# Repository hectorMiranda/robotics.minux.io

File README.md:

## Projects

### Marcebot

The Marcebot is a small, autonomous robot designed for navigation and object avoidance. It uses a differential drive system with two stepper motors and an ultrasonic sensor for obstacle detection. The robot's behavior is controlled by an Arduino Nano, which runs a program that implements three modes: collision avoidance, dead reckoning, and path planning.

- **Collision Avoidance Mode**: The robot moves forward and uses the ultrasonic sensor to detect obstacles. When an obstacle is detected, the robot stops, moves backward, and turns to avoid the obstacle.
- **Dead Reckoning Mode**: The robot follows a predefined path of forward movements and turns.
- **Path Planning Mode**: The robot navigates a path while avoiding obstacles.

The `arduino/marcebot` directory contains the Arduino code for the robot, including the main `.ino` file and the `Robot` class, which provides an API for controlling the robot's movements.

### Digital Clock

This project is a digital clock with an alarm function, built using an ATmega328P microcontroller and a 7-segment display. The clock displays the time in 12-hour format and includes a PM indicator. The user can set the time and alarm using pushbuttons. When the alarm is triggered, it plays a Pac-Man-themed melody.

The `arduino/clock` directory contains the Arduino code for the clock, including the main `.ino` file and the logic for the alarm and display.

### Baremetal Minux

This project is a lightweight, ncurses-based file explorer with multi-tab support and modern features, designed for minimal resource usage and maximum efficiency. It also includes a cryptocurrency wallet and camera functionality.

The `baremetal` directory contains the source code for the file explorer, including the main `minux.cpp` file, the `explorer.cpp` file, and the `error_console.cpp` file, which implements a DOOM-style error console.

### CUDA Status Checker

This project is a Python script that checks the status of the CUDA installation on a system. It verifies the NVIDIA driver, CUDA Toolkit, and CUDA runtime libraries, and it also checks for PyTorch and TensorFlow CUDA support.

The `cuda` directory contains the `cuda_status.py` script.

### ESP32-S3 Camera

This project is a simple web server that streams video from an ESP32-S3 camera module. The server provides a web page with an MJPEG stream from the camera.

The `esp32-s3-cam` directory contains the C++ code for the camera server.

### Galileo

This project contains a collection of Arduino and Python scripts for the Intel Galileo board. The Arduino scripts include examples for creating a web server, an interactive web server, and a Wi-Fi web server with Telnet. The Python scripts include examples for controlling motors and reading from sensors.

The `galileo` directory contains the Arduino and Python scripts.

### GoPiGo

This project is a Python library for controlling the GoPiGo robot. The library provides a simple API for controlling the robot's motors, reading from sensors, and controlling the LEDs.

The `raspberrypi/src` directory contains the `gopigo.py` library.

### SolidWorks

This project contains the SolidWorks assembly files for the MIT-101 project.

The `solidworks` directory contains the SolidWorks files.

## License

This project is licensed under the MIT License. See the `LICENSE` file for details.

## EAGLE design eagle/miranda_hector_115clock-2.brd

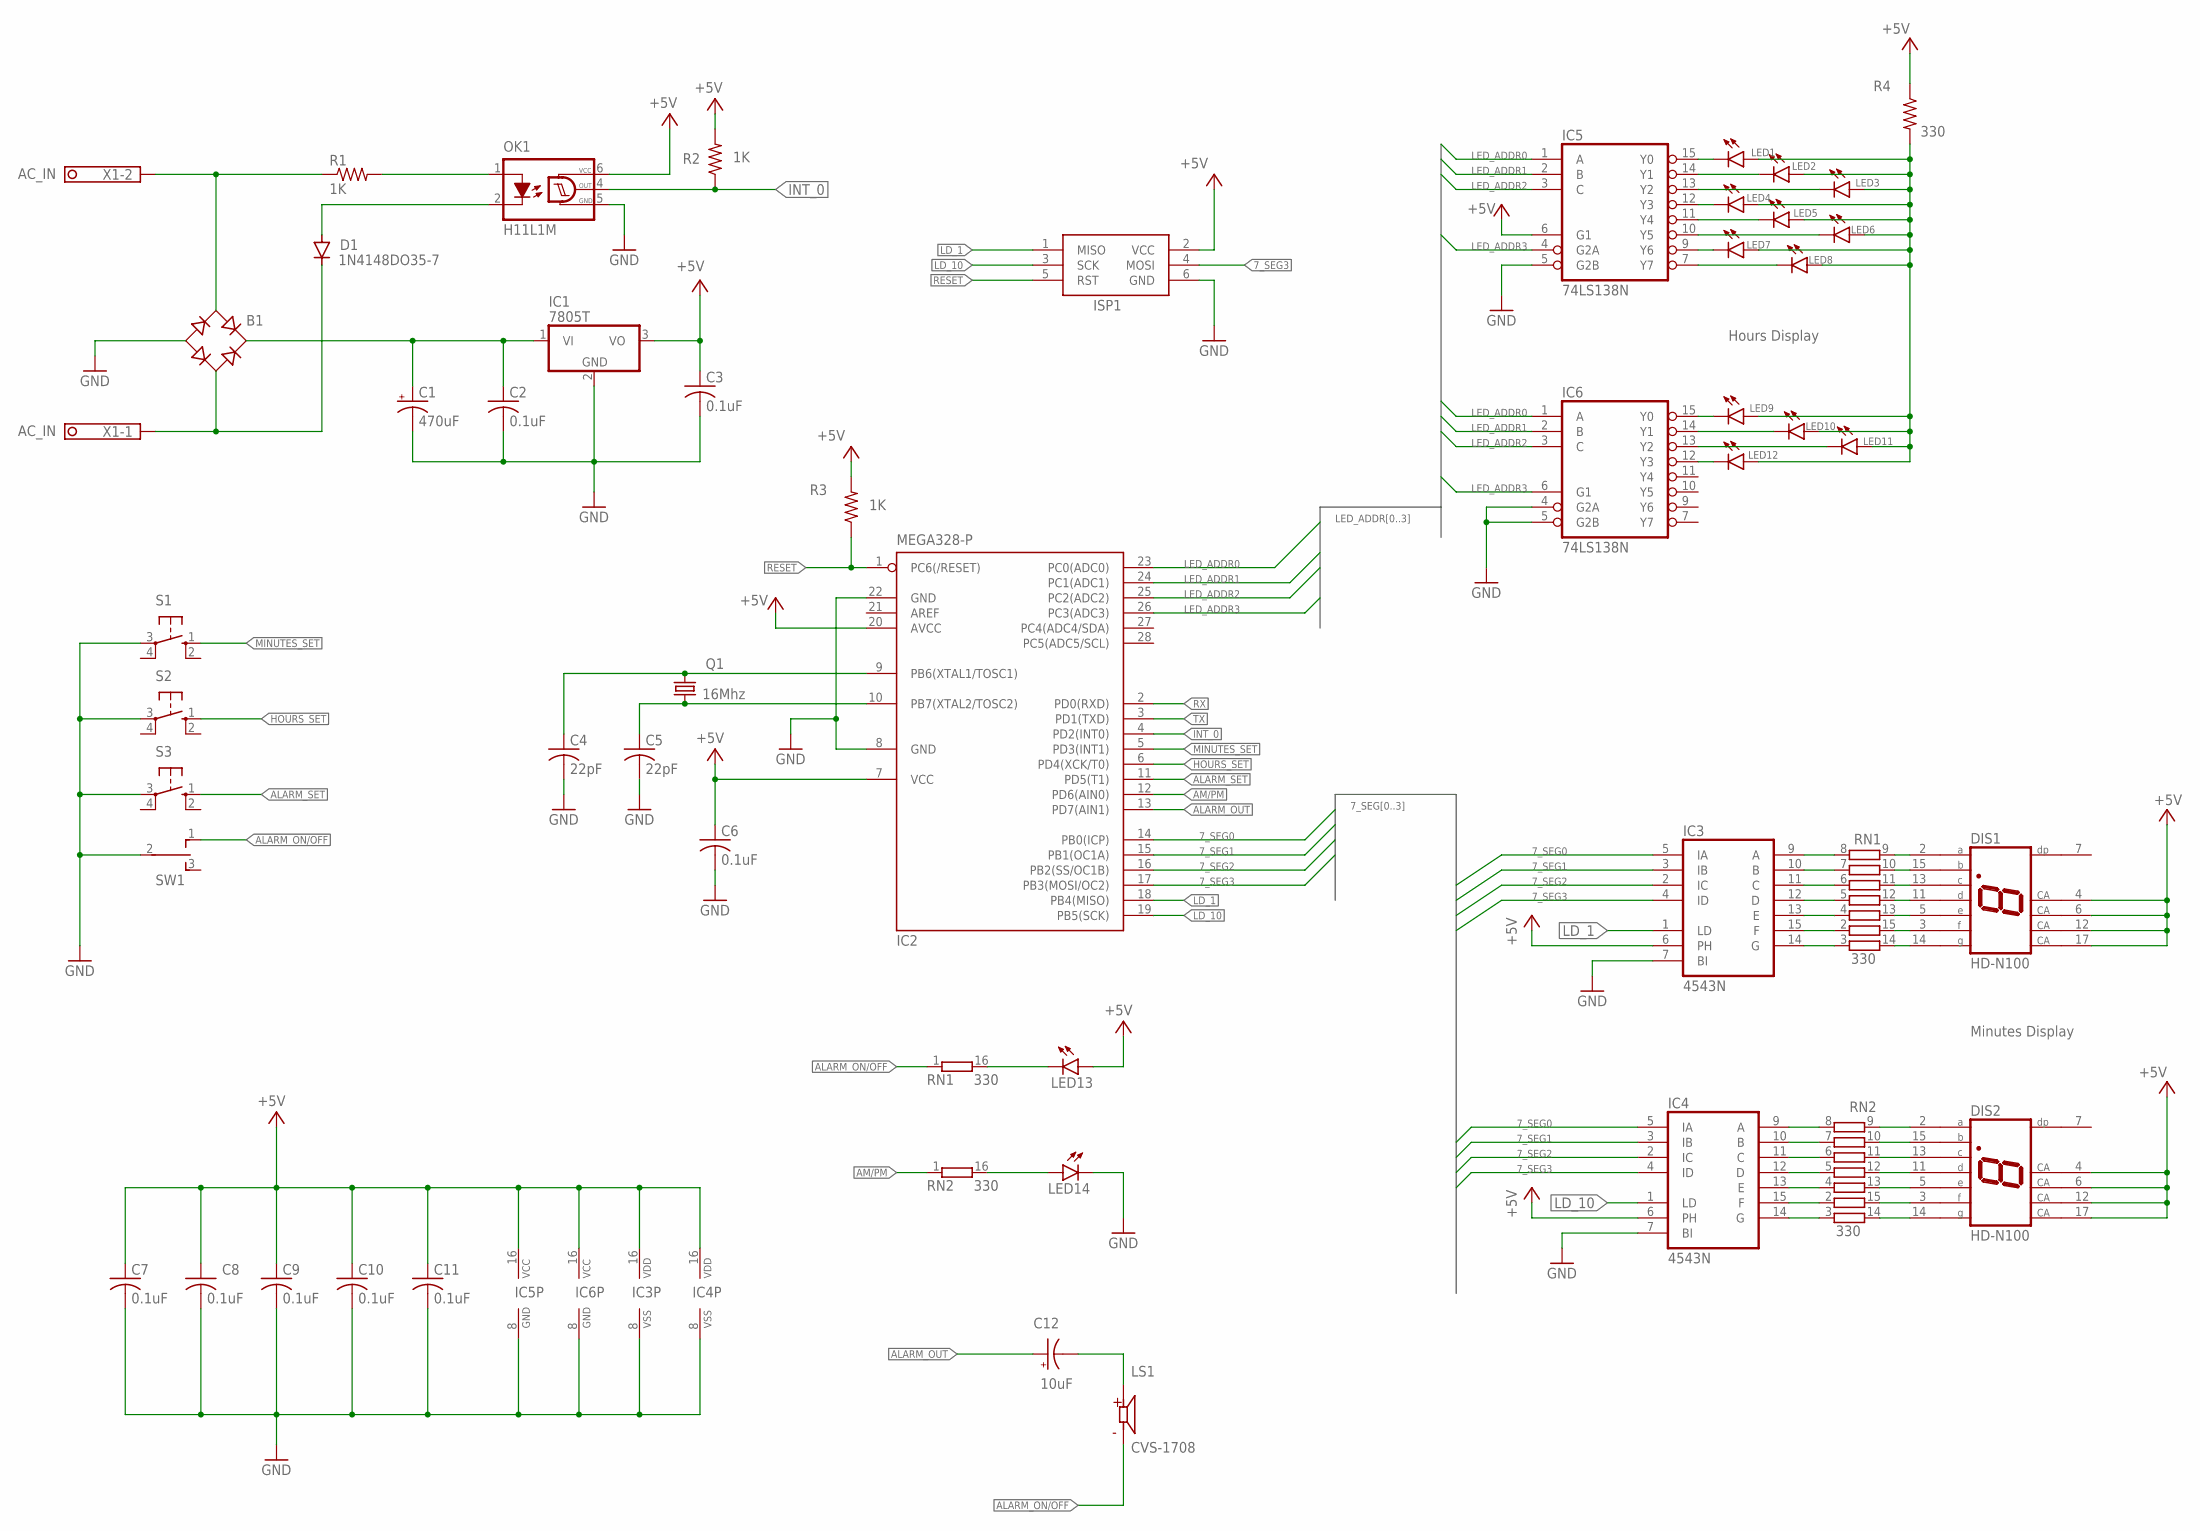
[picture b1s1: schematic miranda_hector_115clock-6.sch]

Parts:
B1: B-DIL
C1: 470uF; E3,5-8
C2, C3, C6, C7, C8, C9, C10, C11: 0.1uF; C025-025X050
C4, C5: 22pF; C025-025X050
C12: 10uF; E2,5-6E
D1: 1N4148DO35-7; DO35-7
DIS1, DIS2: HD-N100; HDSP-Q
IC1: 7805T; TO220H
IC2: MEGA328-P; DIL28-3
IC3, IC4: 4543N; DIL16
IC5, IC6: 74LS138N; DIL16
ISP1: AVRISP-6; AVRISP
LED1, LED2, LED3, LED4, LED5, LED6, LED7, LED8, LED9, LED10, LED11, LED12: LED10MM
LED13, LED14: LED5MM
LS1: CVS-1708; SPKR_CVS-1708
OK1: H11L1M; DIL06
Q1: 16Mhz; HC49/S
R1, R2, R3: 1K; 0204/7
R4: 330; 0204/7
RN1, RN2: 330; DIL16
S1, S2, S3: 10-XX; B3F-10XX
SW1: DIGICLOCK_S5; FOOTPRINT_DIGICLOCK_S5
X1: 1751248

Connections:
7_SEG0: IC2.14 (PB0(ICP)), IC3.5 (IA), IC4.5 (IA)
7_SEG1: IC2.15 (PB1(OC1A)), IC3.3 (IB), IC4.3 (IB)
7_SEG2: IC2.16 (PB2(SS/OC1B)), IC3.2 (IC), IC4.2 (IC)
7_SEG3: IC2.17 (PB3(MOSI/OC2)), IC3.4 (ID), IC4.4 (ID), ISP1.4 (MOSI)
+5V: C3.1, C6.1, C7.1, C8.1, C9.1, C10.1, C11.1, DIS1.4 (CA), DIS1.6 (CA), DIS1.12 (CA), DIS1.17 (CA), DIS2.4 (CA), DIS2.6 (CA), DIS2.12 (CA), DIS2.17 (CA), IC1.3 (VO), IC2.7 (VCC), IC2.20 (AVCC), IC3.6 (PH), IC3.16 (VDD), IC4.6 (PH), IC4.16 (VDD), IC5.6 (G1), IC5.16 (VCC), IC6.16 (VCC), ISP1.2 (VCC), LED13.A, OK1.6 (VCC), R2.2, R3.2, R4.1
ALARM_ON/OFF: LS1.M, RN1.1, SW1.1 (O)
ALARM_OUT: C12.+, IC2.13 (PD7(AIN1))
ALARM_SET: IC2.11 (PD5(T1)), S3.1 (S)
AM/PM: IC2.12 (PD6(AIN0)), RN2.1
GND: B1.-, C1.-, C2.2, C3.2, C4.2, C5.2, C6.2, C7.2, C8.2, C9.2, C10.2, C11.2, IC1.2 (GND), IC2.8 (GND), IC2.22 (GND), IC3.7 (BI), IC3.8 (VSS), IC4.7 (BI), IC4.8 (VSS), IC5.5 (G2B), IC5.8 (GND), IC6.4 (G2A), IC6.5 (G2B), IC6.8 (GND), ISP1.6 (GND), LED14.K (C), OK1.5 (GND), S1.3, S2.3, S3.3, SW1.2
HOURS_SET: IC2.6 (PD4(XCK/T0)), S2.1 (S)
INT_0: IC2.4 (PD2(INT0)), OK1.4 (OUT), R2.1
LD_1: IC2.18 (PB4(MISO)), IC3.1 (LD), ISP1.1 (MISO)
LD_10: IC2.19 (PB5(SCK)), IC4.1 (LD), ISP1.3 (SCK)
LED_ADDR0: IC2.23 (PC0(ADC0)), IC5.1 (A), IC6.1 (A)
LED_ADDR1: IC2.24 (PC1(ADC1)), IC5.2 (B), IC6.2 (B)
LED_ADDR2: IC2.25 (PC2(ADC2)), IC5.3 (C), IC6.3 (C)
LED_ADDR3: IC2.26 (PC3(ADC3)), IC5.4 (G2A), IC6.6 (G1)
MINUTES_SET: IC2.5 (PD3(INT1)), S1.1 (S)
unnamed: B1.AC2, D1.C, X1.1
unnamed: B1.AC1, R1.1, X1.2
unnamed: OK1.1 (A), R1.2
unnamed: D1.A, OK1.2 (C)
unnamed: C4.1, IC2.9 (PB6(XTAL1/TOSC1)), Q1.2
unnamed: C5.1, IC2.10 (PB7(XTAL2/TOSC2)), Q1.1
unnamed: B1.+, C1.+, C2.1, IC1.1 (VI)
unnamed: DIS1.2 (A), RN1.9 (2)
unnamed: DIS1.15 (B), RN1.10 (2)
unnamed: DIS1.13 (C), RN1.11 (2)
unnamed: DIS1.11 (D), RN1.12 (2)
unnamed: DIS1.5 (E), RN1.13 (2)
unnamed: DIS1.3 (F), RN1.15 (2)
unnamed: DIS1.14 (G), RN1.14 (2)
unnamed: IC3.9 (A), RN1.8 (1)
unnamed: IC3.10 (B), RN1.7 (1)
unnamed: IC3.11 (C), RN1.6 (1)
unnamed: IC3.12 (D), RN1.5 (1)
unnamed: IC3.13 (E), RN1.4 (1)
unnamed: IC3.15 (F), RN1.2 (1)
unnamed: IC3.14 (G), RN1.3 (1)
unnamed: DIS2.2 (A), RN2.9 (2)
unnamed: DIS2.15 (B), RN2.10 (2)
unnamed: DIS2.13 (C), RN2.11 (2)
unnamed: DIS2.11 (D), RN2.12 (2)
unnamed: DIS2.5 (E), RN2.13 (2)
unnamed: DIS2.3 (F), RN2.15 (2)
unnamed: DIS2.14 (G), RN2.14 (2)
unnamed: IC4.9 (A), RN2.8 (1)
unnamed: IC4.10 (B), RN2.7 (1)
unnamed: IC4.11 (C), RN2.6 (1)
unnamed: IC4.12 (D), RN2.5 (1)
unnamed: IC4.13 (E), RN2.4 (1)
unnamed: IC4.15 (F), RN2.2 (1)
unnamed: IC4.14 (G), RN2.3 (1)
unnamed: IC5.15 (Y0), LED1.K (C)
unnamed: LED1.A, LED2.A, LED3.A, LED4.A, LED5.A, LED6.A, LED7.A, LED8.A, LED9.A, LED10.A, LED11.A, LED12.A, R4.2
unnamed: IC5.14 (Y1), LED2.K (C)
unnamed: IC5.13 (Y2), LED3.K (C)
unnamed: IC5.12 (Y3), LED4.K (C)
unnamed: IC5.11 (Y4), LED5.K (C)
unnamed: IC5.10 (Y5), LED6.K (C)
unnamed: IC5.9 (Y6), LED7.K (C)
unnamed: IC5.7 (Y7), LED8.K (C)
unnamed: IC6.15 (Y0), LED9.K (C)
unnamed: IC6.14 (Y1), LED10.K (C)
unnamed: IC6.13 (Y2), LED11.K (C)
unnamed: IC6.12 (Y3), LED12.K (C)
unnamed: LED13.K (C), RN1.16 (2)
unnamed: LED14.A, RN2.16 (2)
unnamed: C12.-, LS1.P
RESET: IC2.1 (PC6(/RESET)), ISP1.5 (RST), R3.1
RX: IC2.2 (PD0(RXD))
TX: IC2.3 (PD1(TXD))

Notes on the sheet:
AC_IN
RN1
Minutes Display
Hours Display
RN2

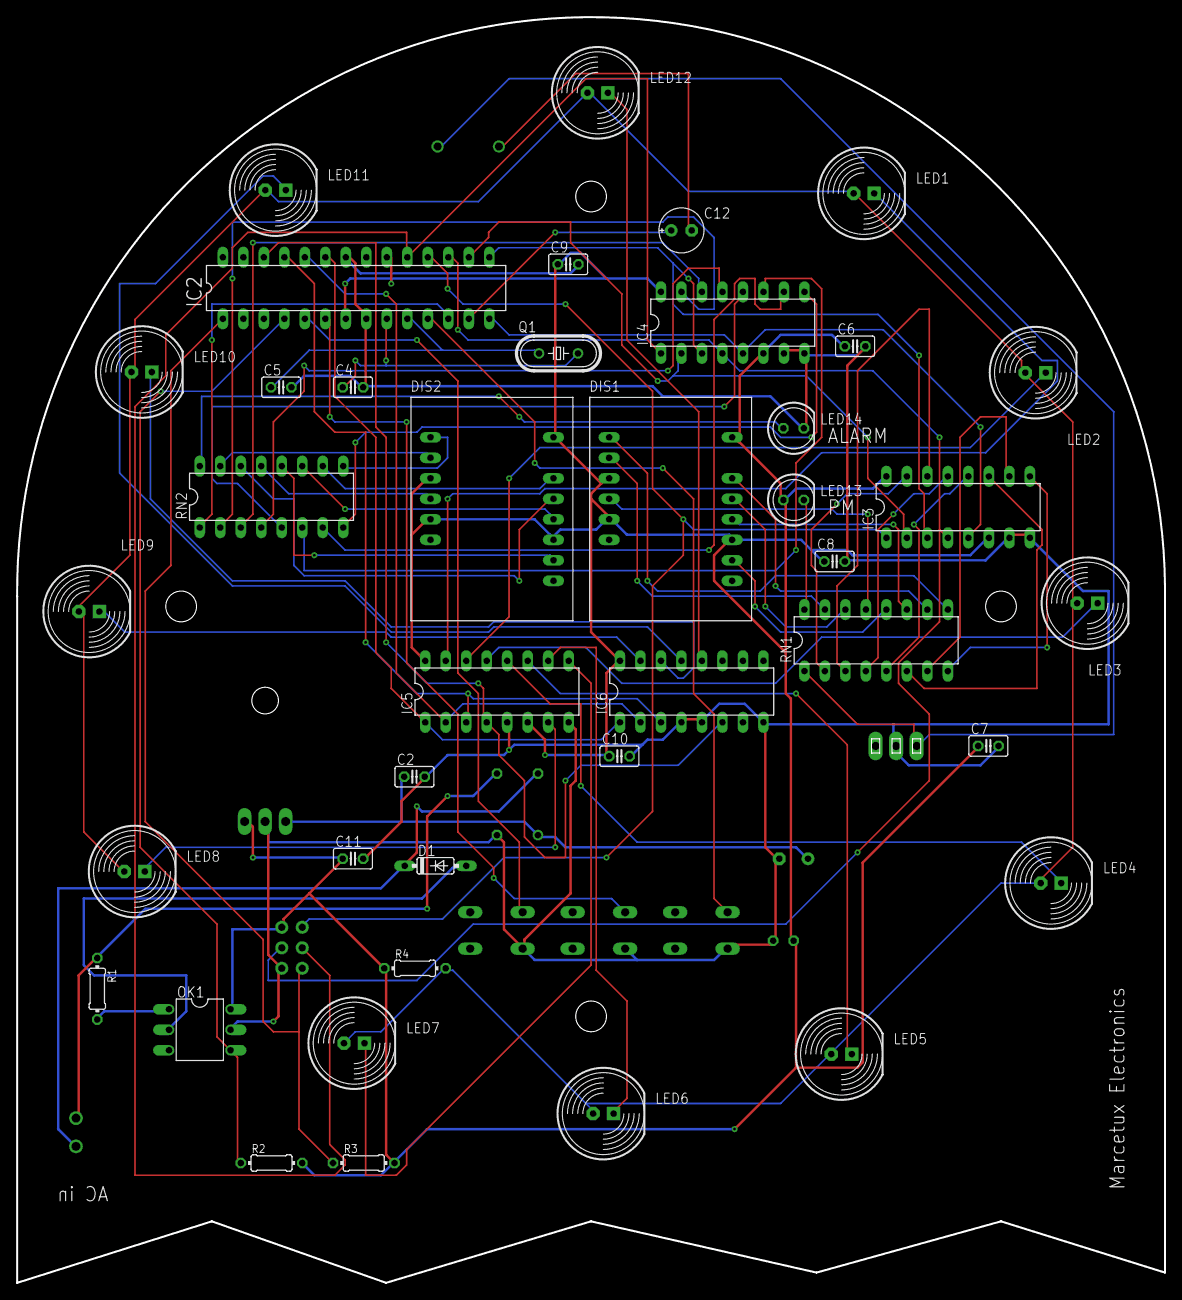
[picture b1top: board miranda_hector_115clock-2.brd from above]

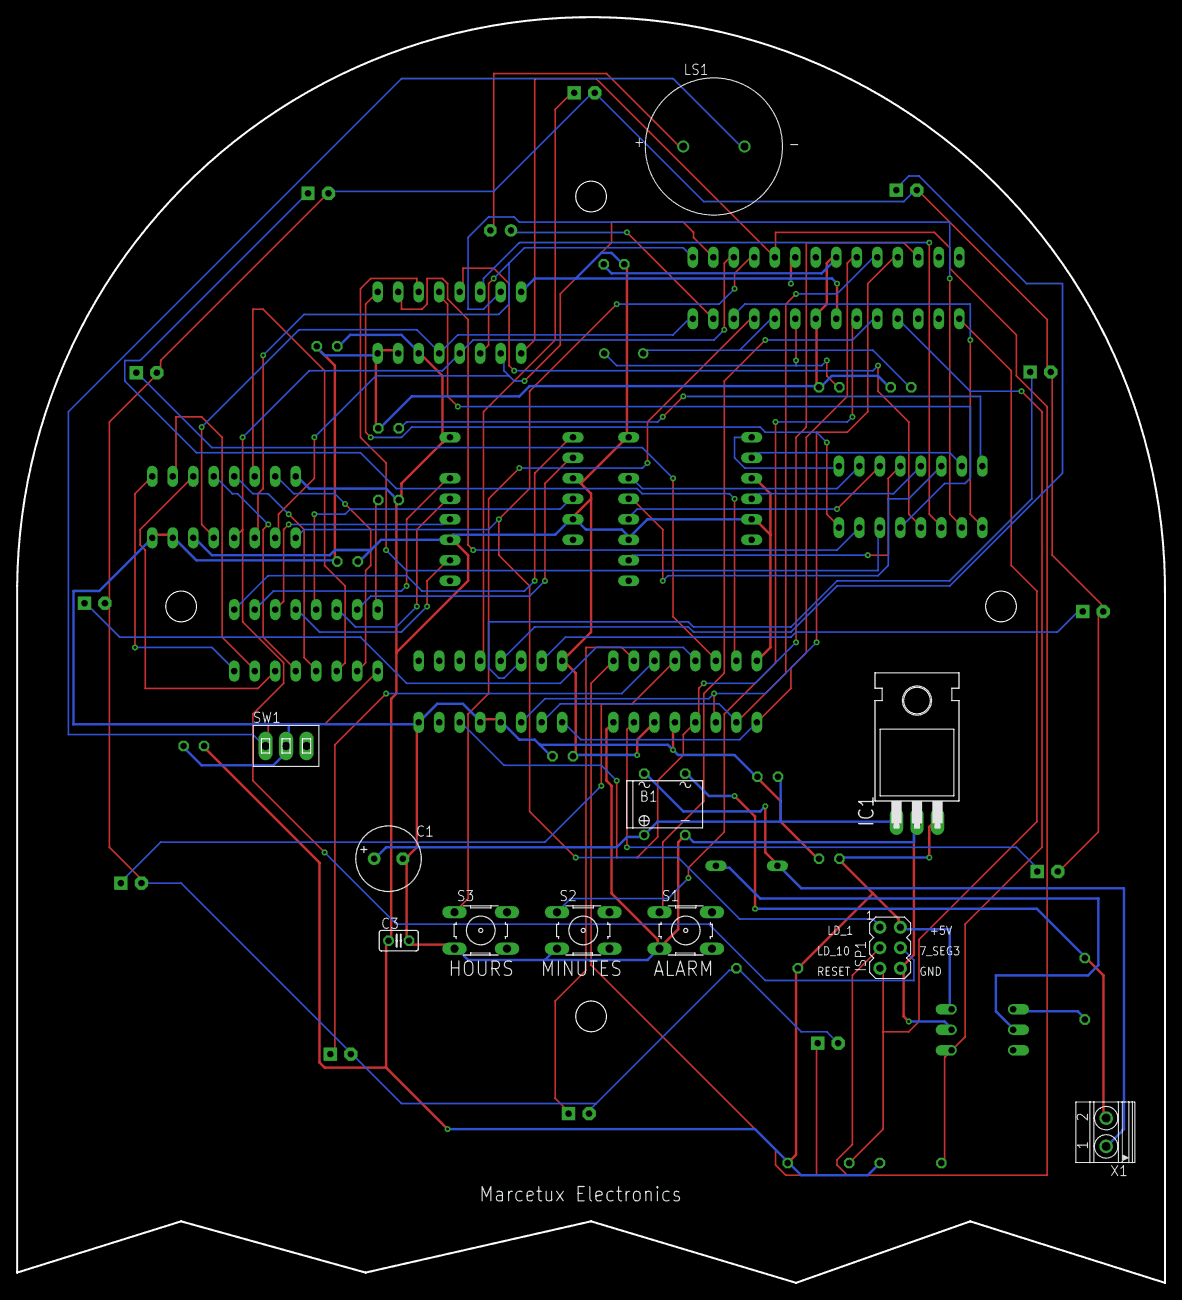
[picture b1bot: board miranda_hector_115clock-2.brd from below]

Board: 2 copper layers, 142.2 x 156.8 mm, 51 parts (11 on the bottom side), 71 nets.

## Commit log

2014-07-30 Adding sketch that initializes and set a static IP allowin us to connect via telnet
2014-07-30 Update StartEthernet.ino
    Update static IP address in comments
2014-07-30 Adding instructions on how to prepare a new linux image
2014-07-30 Update Creating a micro SD image
    Updating documentation
2014-07-30 Delete Creating a micro SD image~
    Deleting temporary file
2014-07-31 Adding webserver code
2014-08-05 Adding interactive webserver example
2014-08-07 Webserver connecting to wifi
2014-08-09 basic handling of key events triggering digital writes.
2014-08-09 Sample code sending PWM signals
2014-08-12 Adding simple object to wrap moving functions
2017-03-21 new structure to support the minux agent
2024-04-25 Adding some pictures with current progress
2024-05-01 adding arduino nano example
2024-05-02 adding stepper coding sample
2024-05-03 placeholder for solidworks files
2024-05-04 solid works progress for robot cover
2024-05-05 Main assembly
2024-05-06 minor updates to readme
2024-05-14 First version using fasdtaccelstep program
2024-05-14 latest version
2024-05-21 including now both challenges
2024-05-22 Adding final designs for robot
2024-05-23 main based adjustments
2024-05-23 m1 base v1
2024-05-24 Adding dwg and new version for main base
2024-05-24 removing dsstore
2024-05-26 trunk door
2024-05-27 front top
2024-05-28 front bottom
2024-05-29 removing zone identifiers
2024-05-30 second version, adjustment needed to secure it easily to the main base
2024-05-31 divider
2024-06-01 Adding fixed right door
2024-06-02 both doors
2024-06-03 new version for cup holder
2024-06-04 final version for bumper cover
2024-06-05 final version for demo
2024-06-05 light holders back
2024-06-06 light holders front
2024-06-07 new front top cover
2024-06-08 more assets..
2024-06-09 some renders
2024-06-10 more images
2024-06-11 final day
2024-06-12 updating readme
2024-06-12 fixes for broken links
2024-06-14 some clarifications in the readme
2024-06-15 adding presentation used for final
2024-06-16 readme updates
2024-06-17 changes to support the new leds
2024-06-19 Adding more photos
2024-07-20 Initial commit for the vision modules
2025-02-24 adding general readme file
2025-03-11 Bare Metal Minux
2025-03-11 Adding readme
2025-03-11 Actually useful documentation
2025-03-11 baremetal minux 0.0.1
2025-03-19 adding support for the Arducam Day-Night Vision for Raspberry Pi
2025-03-19 New settings for makefile
2025-03-19 more settings
2025-03-19 Addind proper command handling
2025-03-19 camera path
2025-03-19 missing separator fix
2025-03-19 now using g++
2025-03-19 fixing malloc issues
2025-03-19 fixing explorer as well
2025-03-19 Adding support for macos
2025-03-19 updating extensions and adding serial monitor
2025-03-21 Adding gpio
2025-03-21 Removing duplicated code
2025-03-21 proper pigio inlcvusion
2025-03-21 .gitignore is now considering object files
2025-03-21 has_includ pigpio
2025-03-21 Platform details on start
2025-03-21 fixed gpioInit
2025-03-21 flags changed
2025-03-21 removed redefinition for has pigio
2025-03-21 multi environment support
2025-03-22 ls defaults now to ls -la
2025-03-22 Fixes for explorer and doom log
2025-03-22 Adding tree command
2025-03-22 Editor and cat command added
2025-03-23 now showing the banner
2025-03-24 added mac support to make file
2025-03-24 Adding history and log commands
2025-03-26 playing notes first iteration
2025-03-26 play scale poc
2025-03-26 adding todo and todo operations
2025-03-27 encryption, decryption, hashing and keypair generation using secp256k1
2025-03-28 wallet command added
2025-03-29 actual implementations for wallet operations
2025-03-31 Readme now has details for wallet command
2025-05-11 Adding instructions for mac and tweaking make file
2025-05-16 Adding screenshot for the PCB v 0.1
    for the clock project
2025-05-16 Update README.md to include clock project
2025-05-16 schematics for clock project
2025-05-20 Adding esp32 cam code
2025-05-20 implementing cameraServer
2025-05-21 sources for nano and esp32 holders
2025-05-22 Eagle files for clock project
2025-05-23 placeholders for minux one board design files
2025-05-28 Adding esp32_mine project to be the foundation for minux one
2025-06-04 Adding STLs for clock project
2025-06-05 including stl for new cover
2025-06-06 cover fixes
2025-06-06 Adding hole for rectifier
2025-06-08 Adding extruded walls
2025-06-08 clock version 0.1
2025-06-11 LEDs now light up in sequence when alarm is triggered, including also solidworks source files
2025-06-12 pictures for the final clock project
2025-06-14 first attempt to generate key concepts tool for classmates
2025-06-19 Adding cuda testing scripts
2025-06-20 checking nvidia smi driver
2025-06-20 adding setup instructions
2025-06-21 readme for cuda
2025-06-24 Showing pending item instructions only for missing items
2025-06-27 updating readmes
2025-06-29 updating paths
2025-06-30 proper README.md added for baremetal minux
2025-07-02 cuda attempt
2025-07-02 WSL fixes
2025-07-03 if minux doesnt support a command the shell may
2025-07-04 removing obvious comments
2025-07-05 comment clean up
2025-07-08 a top like tool but for cuda
2025-07-09 cuda top on wsl
2025-07-10 cuda rewritte
2025-07-25 Adding initial code for OLED screen
2025-07-25 better structure and consistency
2025-07-25 now running with platformio
2025-07-25 Using nanoatmega328new
2025-07-25 Added a simulated odometer for the line follower robot
2025-07-25 better structure to run the demos
2025-07-25 First iteration for generic dashboard
2025-07-25 Adding buzzer
2025-07-25 buzzer now doesnt block main oled
2025-07-26 Adding support for up button
2025-07-26 last commit for this POC, project needs new repository
2025-07-26 Cleaning up this before archiving... trying to bring back a 90's computer experience
2025-07-26 Windows 3.1 style added
